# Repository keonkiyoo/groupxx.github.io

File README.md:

# groupxx.github.io

Team Smart Cane - T06
Group Members: Shadman Shamin, Keon Yoo, Nate Pham, Dusan Micic

Project Description: The development and implementation of a smart cane that read surrounding environment and measures distance between the user and obstacles. The cane is for everybody who uses a cane and geared towards elderly population to help them navigate the streets and pedestrians safely. Based on the threshold safe distance the cane sends a haptic feedback to user to notify/alert the user of nearby obstacles so that they can avoid the obstacles safely.

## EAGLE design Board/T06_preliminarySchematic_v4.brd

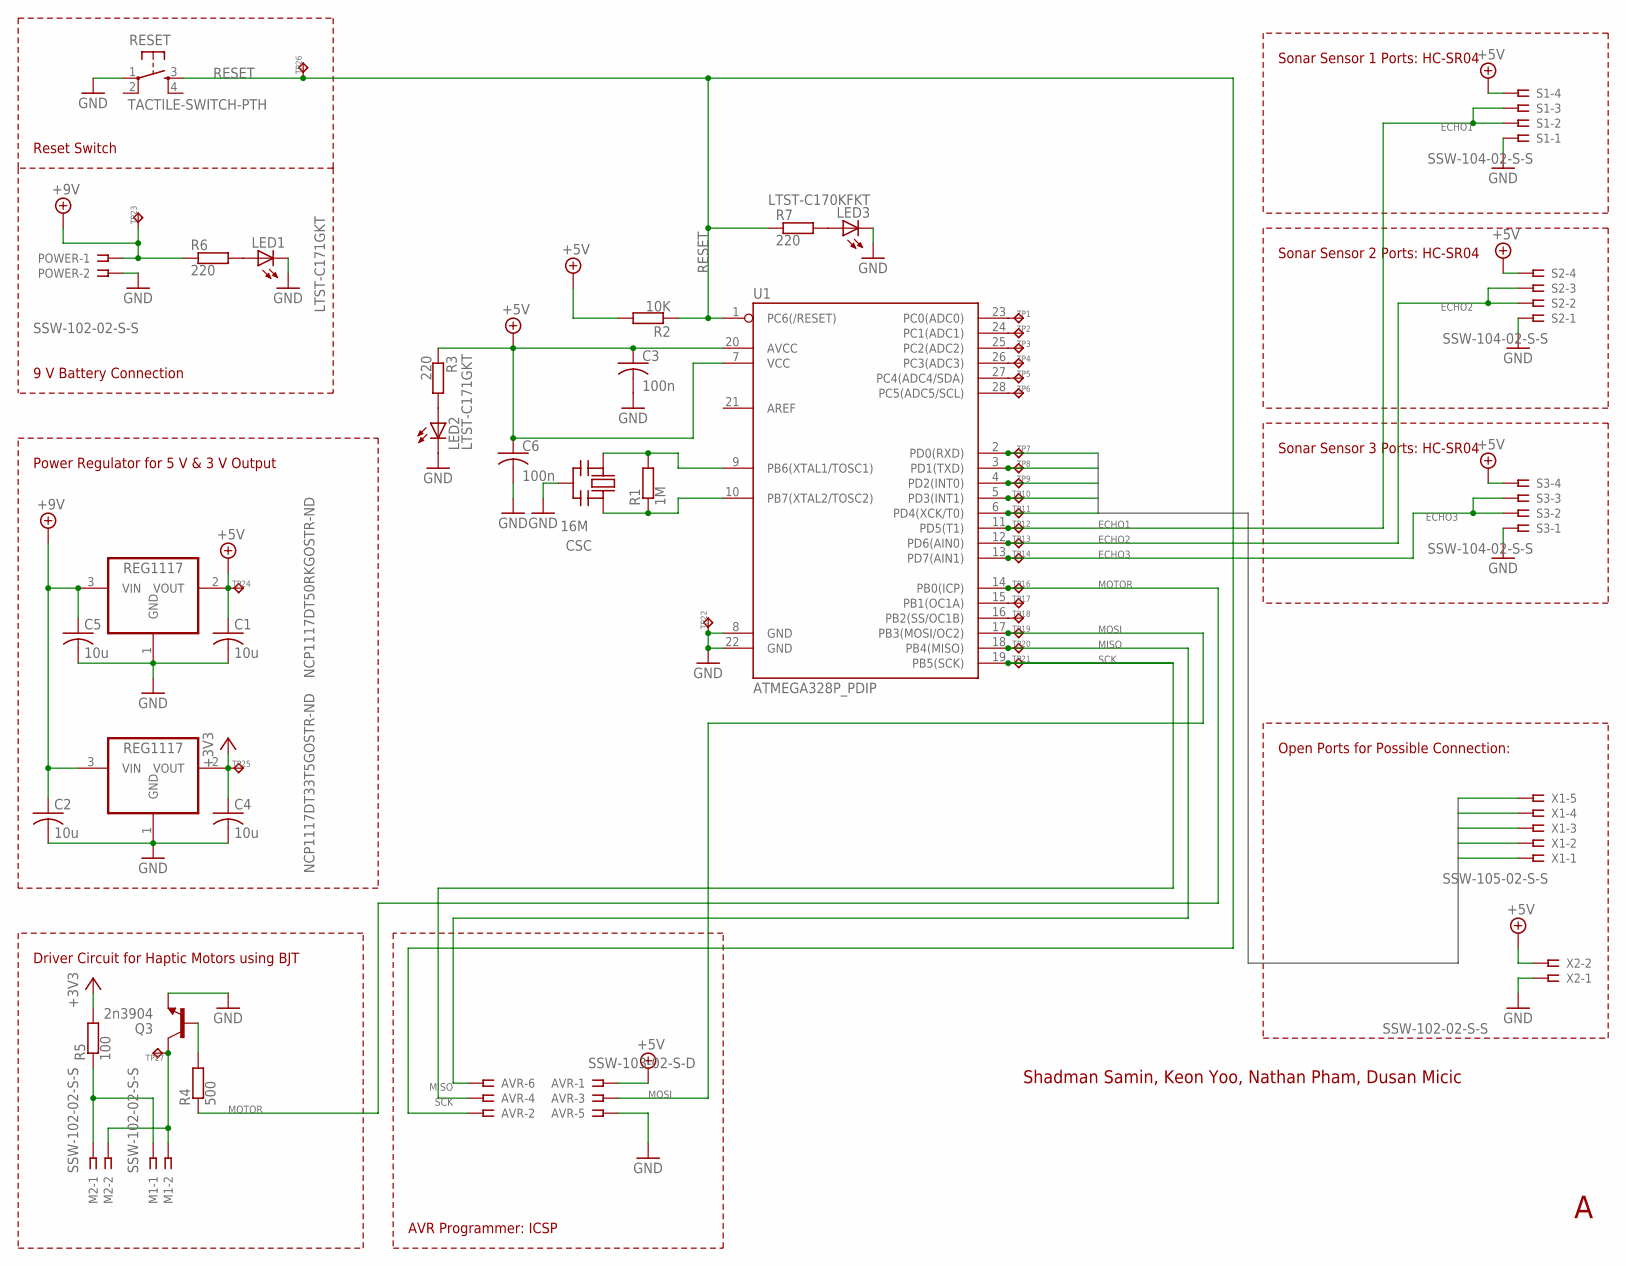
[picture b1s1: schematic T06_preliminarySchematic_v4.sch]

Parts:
AVR: SSW-103-02-S-D
C1, C2, C4, C5: 10u; C0805K
C3, C6: 100n; C0805K
CSC: 16M; CSTCR-G
LED1: LTST-C171GKT; CHIPLED_0805
LED2: LTST-C171GKT; CHIP-LED0805
LED3: LTST-C170KFKT; CHIP-LED0805
M1, M2: SSW-102-02-S-S
NCP1117DT33T5GOSTR-ND, NCP1117DT50RKGOSTR-ND: REG1117; SOT223
POWER: SSW-102-02-S-S
Q3: 2n3904; TO-92
R1: 1M; R0603
R2: 10K; R0603
R3, R6, R7: 220; R0603
R4: 500; R0603
R5: 100; R0603
RESET: TACTILE-SWITCH-PTH; TAC-SWITCH-PTH
S1, S2, S3: SSW-104-02-S-S
TP1, TP2, TP3, TP4, TP5, TP6, TP7, TP8, TP9, TP10, TP11, TP12, TP13, TP14, TP16, TP17, TP18, TP19, TP20, TP21, TP22, TP23, TP24, TP25, TP26, TP27: TPPAD1-13; P1-13
U1: ATMEGA328P_PDIP; DIL28-3
X1: SSW-105-02-S-S
X2: SSW-102-02-S-S

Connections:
+3V3: C4.1, NCP1117DT33T5GOSTR-ND.2 (VOUT), R5.2, TP25.TP
+5V: AVR.1, C1.1, C3.1, C6.1, NCP1117DT50RKGOSTR-ND.2 (VOUT), R2.2, R3.1, S1.4, S2.4, S3.4, TP24.TP, U1.7 (VCC), U1.20 (AVCC), X2.2
+9V: C2.1, C5.1, NCP1117DT33T5GOSTR-ND.3 (VIN), NCP1117DT50RKGOSTR-ND.3 (VIN), POWER.1, R6.1, TP23.TP
BU0: TP7.TP, U1.2 (PD0(RXD)), X1.1
BU1: TP8.TP, U1.3 (PD1(TXD)), X1.2
BU2: TP9.TP, U1.4 (PD2(INT0)), X1.3
BU3: TP10.TP, U1.5 (PD3(INT1)), X1.4
BU4: TP11.TP, U1.6 (PD4(XCK/T0)), X1.5
D16: TP18.TP, U1.16 (PB2(SS/OC1B))
ECHO1: S1.2, S1.3, TP12.TP, U1.11 (PD5(T1))
ECHO2: S2.2, S2.3, TP13.TP, U1.12 (PD6(AIN0))
ECHO3: S3.2, S3.3, TP14.TP, U1.13 (PD7(AIN1))
GND: AVR.5, C1.2, C2.2, C3.2, C4.2, C5.2, C6.2, CSC.2 (GND), LED1.C, LED2.C, LED3.C, NCP1117DT33T5GOSTR-ND.1 (GND), NCP1117DT50RKGOSTR-ND.1 (GND), POWER.2, Q3.1 (E), RESET.1, S1.1, S2.1, S3.1, TP22.TP, U1.8 (GND), U1.22 (GND), X2.1
MISO: AVR.6, TP20.TP, U1.18 (PB4(MISO))
MOSI: AVR.3, TP19.TP, U1.17 (PB3(MOSI/OC2))
MOTOR: R4.1, TP16.TP, U1.14 (PB0(ICP))
unnamed: CSC.3 (OUT), R1.1, U1.10 (PB7(XTAL2/TOSC2))
unnamed: CSC.1 (IN), R1.2, U1.9 (PB6(XTAL1/TOSC1))
unnamed: TP1.TP, U1.23 (PC0(ADC0))
unnamed: TP2.TP, U1.24 (PC1(ADC1))
unnamed: M1.1, M2.1, R5.1
unnamed: TP3.TP, U1.25 (PC2(ADC2))
unnamed: LED1.A, R6.2
unnamed: LED2.A, R3.2
unnamed: LED3.A, R7.2
unnamed: Q3.2 (B), R4.2
unnamed: M1.2, M2.2, Q3.3 (C), TP27.TP
unnamed: TP4.TP, U1.26 (PC3(ADC3))
unnamed: TP5.TP, U1.27 (PC4(ADC4/SDA))
unnamed: TP6.TP, U1.28 (PC5(ADC5/SCL))
unnamed: TP17.TP, U1.15 (PB1(OC1A))
RESET: AVR.2, R2.1, R7.1, RESET.3, TP26.TP, U1.1 (PC6(/RESET))
SCK: AVR.4, TP21.TP, U1.19 (PB5(SCK))

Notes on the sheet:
9 V Battery Connection
Driver Circuit for Haptic Motors using BJT
Sonar Sensor 3 Ports: HC-SR04
Sonar Sensor 2 Ports: HC-SR04
Sonar Sensor 1 Ports: HC-SR04
Shadman Samin, Keon Yoo, Nathan Pham, Dusan Micic
Reset Switch
Power Regulator for 5 V & 3 V Output
AVR Programmer: ICSP
Open Ports for Possible Connection:

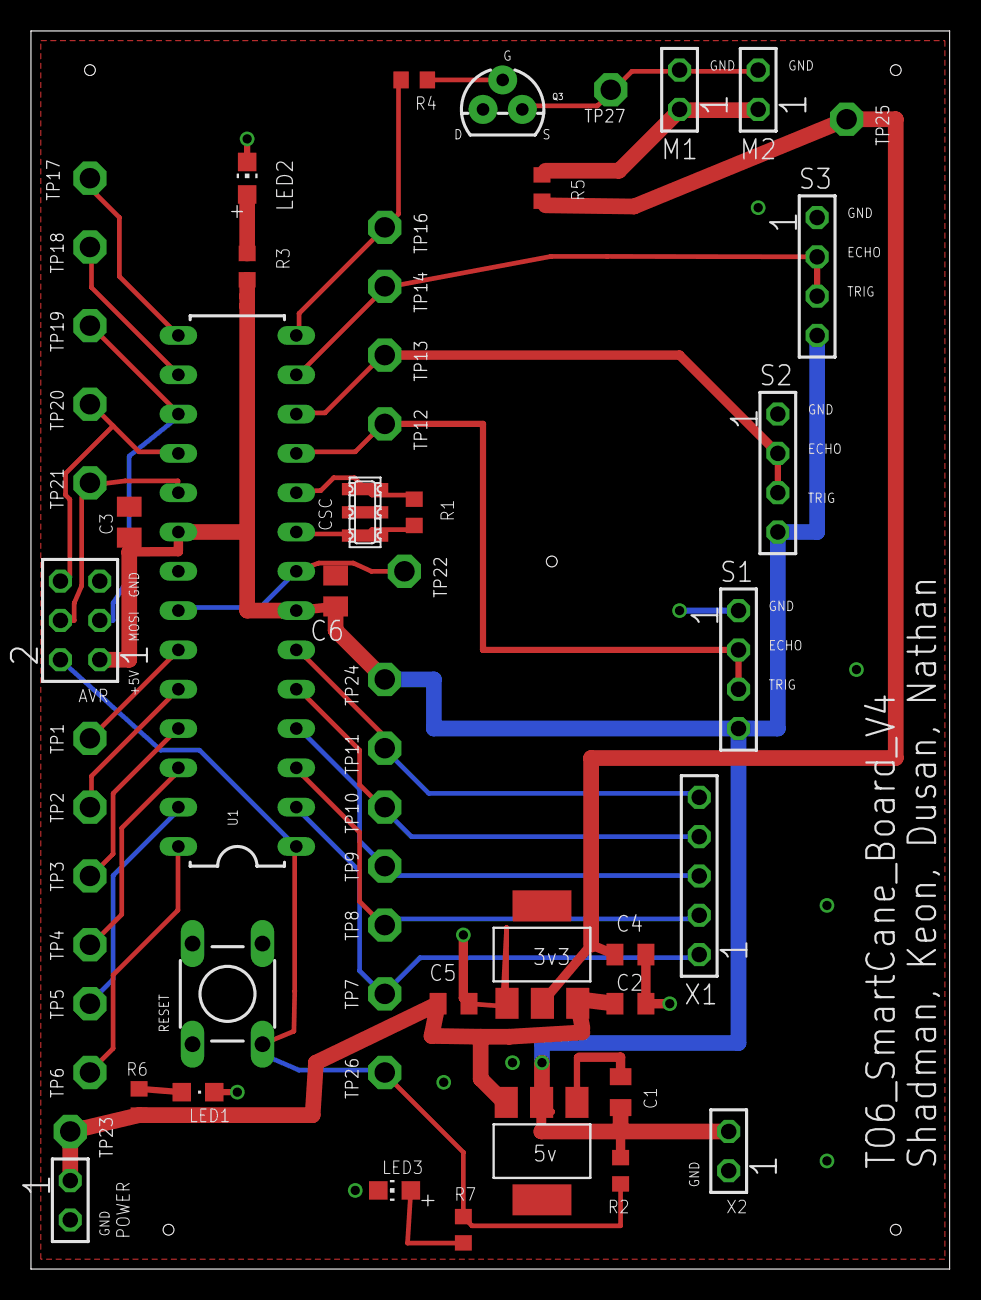
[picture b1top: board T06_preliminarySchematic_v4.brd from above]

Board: 2 copper layers, 59.4 x 80.0 mm, 57 parts (0 on the bottom side), 33 nets.

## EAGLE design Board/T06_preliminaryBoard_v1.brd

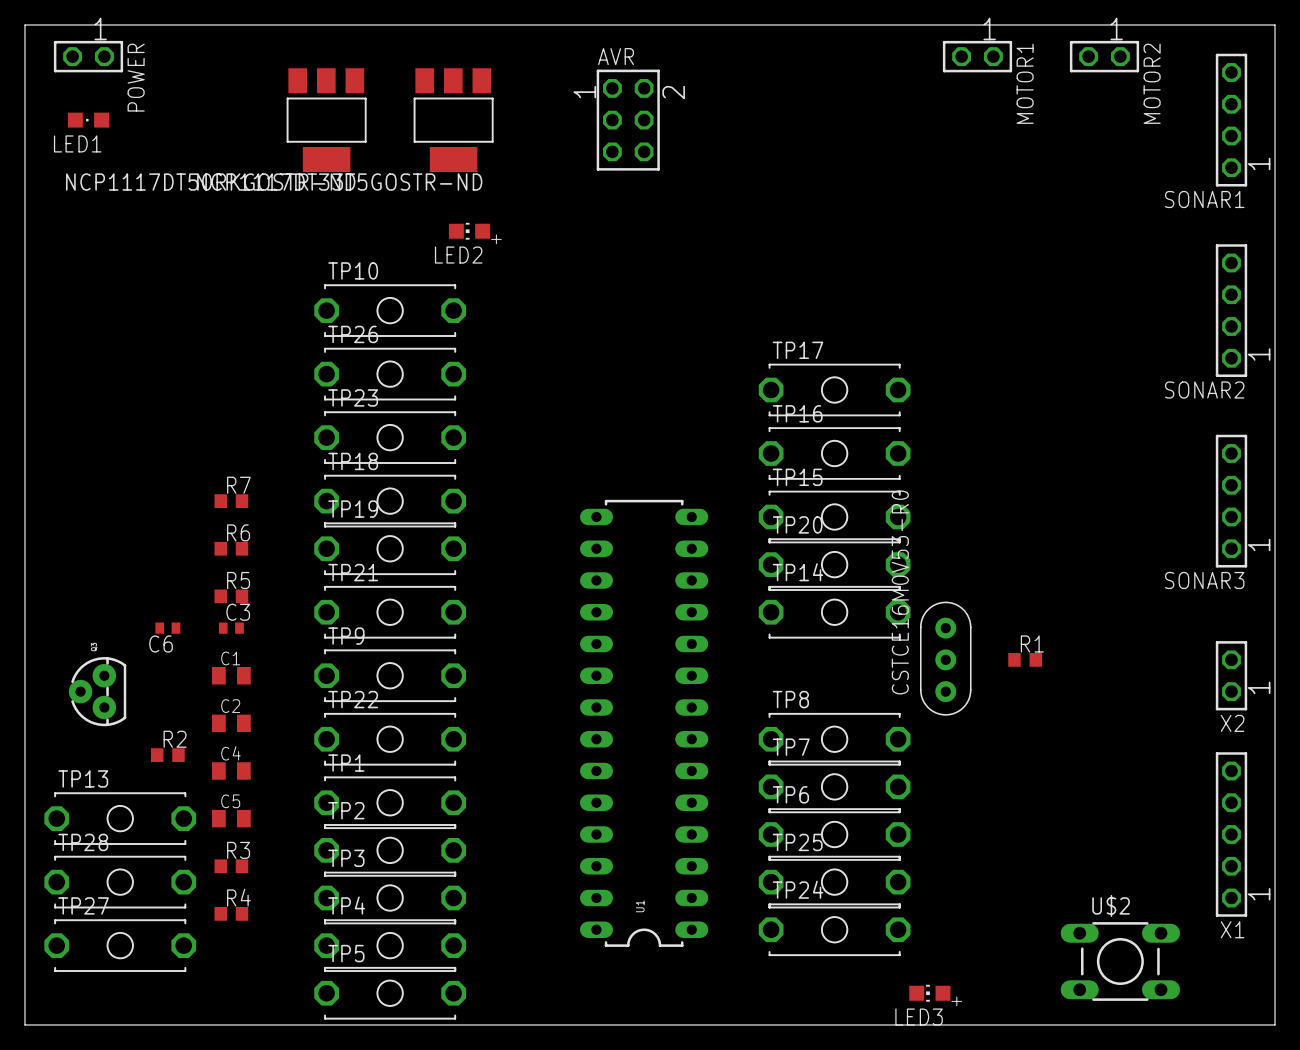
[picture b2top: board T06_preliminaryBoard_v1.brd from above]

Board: 2 copper layers, 100.0 x 80.0 mm, 57 parts (0 on the bottom side), 33 nets, no tracks yet.

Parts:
AVR: SSW-103-02-S-D
C1, C2, C4, C5: 10u; C0805K
C3, C6: 100n; C1005
CSTCE16M0V53-R0: 16M; CERM_OSC
LED1: LTST-C171GKT; CHIPLED_0805
LED2: LTST-C171GKT; CHIP-LED0805
LED3: LTST-C170KFKT; CHIP-LED0805
MOTOR1, MOTOR2: SSW-102-02-S-S
NCP1117DT33T5GOSTR-ND, NCP1117DT50RKGOSTR-ND: REG1117; SOT223
POWER: SSW-102-02-S-S
Q3: 2n3904; TO-92
R1: 1M; R0603
R2: 10K; R0603
R3, R6, R7: 220; R0603
R4: 500; R0603
R5: 100; R0603
SONAR1, SONAR2, SONAR3: SSW-104-02-S-S
TP1, TP2, TP3, TP4, TP5, TP6, TP7, TP8, TP9, TP10, TP13, TP14, TP15, TP16, TP17, TP18, TP19, TP20, TP21, TP22, TP23, TP24, TP25, TP26, TP27, TP28: MPB1
U1: ATMEGA328P_PDIP; DIL28-3
U$2: TACTILE-SWITCH-PTH; TAC-SWITCH-PTH
X1: SSW-105-02-S-S
X2: SSW-102-02-S-S

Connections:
+3V3: C4.1, NCP1117DT33T5GOSTR-ND.2, R5.2, TP10.1, TP10.1@1
+5V: AVR.1, C1.1, C3.1, C6.1, NCP1117DT50RKGOSTR-ND.2, R2.2, R3.1, SONAR1.4, SONAR2.4, SONAR3.4, TP9.1, TP9.1@1, U1.7, U1.20, X2.2
+9V: C2.1, C5.1, NCP1117DT33T5GOSTR-ND.3, NCP1117DT50RKGOSTR-ND.3, POWER.1, R6.1, TP26.1, TP26.1@1
BU0: TP25.1, TP25.1@1, U1.2, X1.1
BU1: TP24.1, TP24.1@1, U1.3, X1.2
BU2: TP6.1, TP6.1@1, U1.4, X1.3
BU3: TP7.1, TP7.1@1, U1.5, X1.4
BU4: TP8.1, TP8.1@1, U1.6, X1.5
D16: TP19.1, TP19.1@1, U1.16
ECHO1: SONAR1.2, TP14.1, TP14.1@1, U1.11
ECHO2: SONAR2.2, TP15.1, TP15.1@1, U1.12
ECHO3: SONAR3.2, TP16.1, TP16.1@1, U1.13
GND: AVR.5, C1.2, C2.2, C3.2, C4.2, C5.2, C6.2, CSTCE16M0V53-R0.P$2, LED1.C, LED2.C, LED3.C, NCP1117DT33T5GOSTR-ND.1, NCP1117DT50RKGOSTR-ND.1, POWER.2, Q3.1, SONAR1.1, SONAR2.1, SONAR3.1, U1.8, U1.22, U$2.1, X2.1
MISO: AVR.6, TP21.1, TP21.1@1, U1.18
MOSI: AVR.3, TP20.1, TP20.1@1, U1.17
MOTOR: R4.1, TP17.1, TP17.1@1, U1.14
unnamed: CSTCE16M0V53-R0.P$3, R1.1, U1.10
unnamed: CSTCE16M0V53-R0.P$1, R1.2, U1.9
unnamed: TP23.1, TP23.1@1, U1.23
unnamed: TP1.1, TP1.1@1, U1.24
unnamed: MOTOR1.1, MOTOR2.1, R5.1
unnamed: TP2.1, TP2.1@1, U1.25
unnamed: LED1.A, R6.2
unnamed: LED2.A, R3.2
unnamed: LED3.A, R7.2
unnamed: Q3.2, R4.2
unnamed: MOTOR1.2, MOTOR2.2, Q3.3, TP13.1, TP13.1@1
unnamed: TP3.1, TP3.1@1, U1.26
unnamed: TP4.1, TP4.1@1, U1.27
unnamed: TP5.1, TP5.1@1, U1.28
RESET: AVR.2, R2.1, R7.1, TP27.1, TP27.1@1, TP28.1, TP28.1@1, U1.1, U$2.3
SCK: AVR.4, TP22.1, TP22.1@1, U1.19
TRIG: SONAR1.3, SONAR2.3, SONAR3.3, TP18.1, TP18.1@1, U1.15

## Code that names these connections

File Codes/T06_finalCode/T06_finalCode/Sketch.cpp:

// Final Code - T06 Smart Cane
// Authors: Shadman Samin, Nathan Pham, Keon Yoo, Shadman Samin 
// Algorithm to find the distance between sensors and obstacles

#include <Arduino.h>

void setup();
void loop(); // Function for While(1) loop


// Initialization of the pin
int echo1 = 5; // ATMEGA328P Pin PD5
int echo2 = 6; // ATMEGA328P Pin PD6 
int echo3 = 7; // ATMEGA328P Pin PD7
int Motor = 8; // ATMEGA328P Pin PB0

void TriggerRead(int echoPin); // Function to send 10 us (atleast) long 
long PulseWidth(int echoPin);  // Function to hear the Echo pin and calculate the distance


int constantDistance_1 = 10; // The sensor one should have atleast 50 cm or less to detect obstacles
int constantDistance_2 = 5; // The sensor two should have atleast 20 cm or less to detect obstacles
int constantDistance_3 = 10; // The sensor three should have atleast 20 cm or less to detect obstacles
int i = 1;

void setup() {
  pinMode(Motor, OUTPUT); // Declare the LED as an output pin
  digitalWrite(Motor, LOW); //Declare the LED to be LOW initially
}

void loop() { 
// The continuous while loop continuously hears for the outputs from the sensors 1,2,3, and adjusts the conditional statements
// to avoid random errors which often is caused by random jitters. So we avoid very low values and ignore them.
// If either of the three sensors senses objects it turns on the motors to alert the user.	


	if((PulseWidth(echo2) < constantDistance_2) || (PulseWidth(echo3) < constantDistance_3)){
		digitalWrite(Motor, HIGH); // Turn on the motor if they fall within range
		}
	else {
		digitalWrite(Motor, LOW); //  Turn it off if it is not within range
	}
}

// Send atleast 10 us trigger
void TriggerRead(int echoPin) {
  delay(20);
  pinMode(echoPin, OUTPUT);
  digitalWrite(echoPin, LOW);  // Added this line
  delayMicroseconds(10); // Added this line
  digitalWrite(echoPin, HIGH);
  delayMicroseconds(20); // Added this line
  digitalWrite(echoPin, LOW);
}

// after the trigger is sent the program waits for a pulse, and using interrupts and a counter within the arduino librarfy it measures the length 
// of the pulse 
long PulseWidth(int echoPin) {
  long duration, distance;
  TriggerRead(echoPin);
  pinMode(echoPin, INPUT);
  duration = pulseIn(echoPin, HIGH);
  
  // ... The ultrasonic sensors waits for a pulse to come back and the pulse width gives us the length of the pulse.
  // Using the duration of the pulse we can measure the distance travelled. 
    // The speed of sound is 340 m/s or 29 microseconds per centimeter.
    // The ping travels out and back, so to find the distance of the
    // object we take half of the distance travelled.
  // Hence, Distance = (0.5*Duration)/29.1
  
  distance = (duration / 2) / 29.4;
  return distance;
}

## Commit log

2015-10-12 Homework 2
2015-10-26 3D CAD Design
2015-10-26 Product Design Specifications
2015-11-01 Schematic
2015-11-01 Nate Pham - Log
2015-11-02 TimeLine
2015-11-05 DataSheets
2015-11-05 Made Changes suggested by Andrew. Made a bus connection for possible future port connections. Also, add AVR Programming Chip to code it in.
2015-11-05 Changed the LED package numbers. Added a Orange LED to the Reset Switch. This goes low when the reset is pressed. Fixed the bypass capacitor problems. Added 100nF bypass capacitor to the VCC and AVCC
2015-11-05 Made a new file for Bill of Materials that needs to be ordered as we go along. NEED to be ordered by next week
2015-11-05 First version of the board with no routing. Next stage we need to route the wires.
2015-11-05 Rough board. Routing still needs to be done
2015-11-06 Dummy change in Bill
2015-11-06 Schematic Revision
2015-11-06 Revert "Schematic Revision"
    This reverts commit 48704319808d7b4bc4e80a9d6127979d2afba1c1.
2015-11-08 made changes to the schematic. Used a different package for the test points as through hole one pin P1-13. Reflected in the schematic. Dusan needs to change and reflect in on the board
2015-11-08 making sure I can do git right before I start changing stuff
2015-11-08 still trying to figutr out git
2015-11-08 practice makes perfect
2015-11-08 board done and routed, managed to do with only 1 via and no air wires
2015-11-09 final design with no drc errors finished
2015-11-09 Changes reflected in the board. Changes made in the master branch. - Dusan
2015-11-09 Testing Branch
2015-11-09 added regulator names
2015-11-09 BOM is done
2015-11-09 changed 500 ohm to 510 ohm
2015-11-09 created version 4 of the board, project and schematic
2015-11-10 Andrews suggestions implemented, still unsure what package sizes he wants us to fix
2015-11-11 Added mounting holes
2015-11-11 added ultrasonic sensor datasheet
2015-11-11 board minor changes
2015-11-12 Built the prototype. The sensor doesnt allow us the trigger all the sensors in parallel. So we are using individual pins to trigger the sensors. That is reflected in this revision
2015-11-12 Board and project files are removed from the schematic folder to only host schematic files
2015-11-12 Version 4 schematic added to the schematic folder to reflect those changes
2015-11-12 Arduino Prototype Code Version 1
2015-11-13 Made changes to the cap size from 1005 to 0805
2015-11-13 atempted to fix tnames layer, not sure what he meant, it looks fine to me
2015-11-13 Nade some visual changes to TNAMES on the board so that they are not overlapping. Added pin Names to AVR ISP
2015-11-13 minor adjustments
2015-11-13 Components for board ordered. Quantity and price and status reflected on the Bill of Materials
2015-11-16 Homework 5. System Model Design final version
2015-11-16 Made changes to the bill of materials. Updated the status of shipment
2015-11-16 Updated Git with new component datasheets to reflect the latest design
2015-11-16 Updated the BOM with current shipment status and board order
2015-11-20 Made changes to the BOM based on current shipment status
2015-11-24 Final Code Version Uploaded - Using Arduino CPP library and arduino Header files
2015-11-25 Test plan for the final prototype
2015-11-30 logs
2015-12-01 updated log
2015-12-09 Test file
2015-12-09 Deleted Test
2015-12-10 Update HW
2015-12-10 pds update
2015-12-10 Final Code Changes made, eventually two sensor trigger are used to drive the motor circuit. BJT is replaced with NMOS for a faster switching frequency and response.
2015-12-11 Shadman Log
2015-12-11 weekly logs and wpr
2015-12-11 Revert "weekly logs and wpr"
    This reverts commit 4d105b75db60a27a60950cd3fc96f8da6126b172.
2015-12-11 board dimension meausre
2015-12-11 TimeLine hw revision
2015-12-11 Presentation Slides

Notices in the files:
parts and their libraries:
SparkFun-DiscreteSemi: Licensing: Creative Commons ShareAlike 4.0 International - https://creativecommons.org/licenses/by-sa/4.0
